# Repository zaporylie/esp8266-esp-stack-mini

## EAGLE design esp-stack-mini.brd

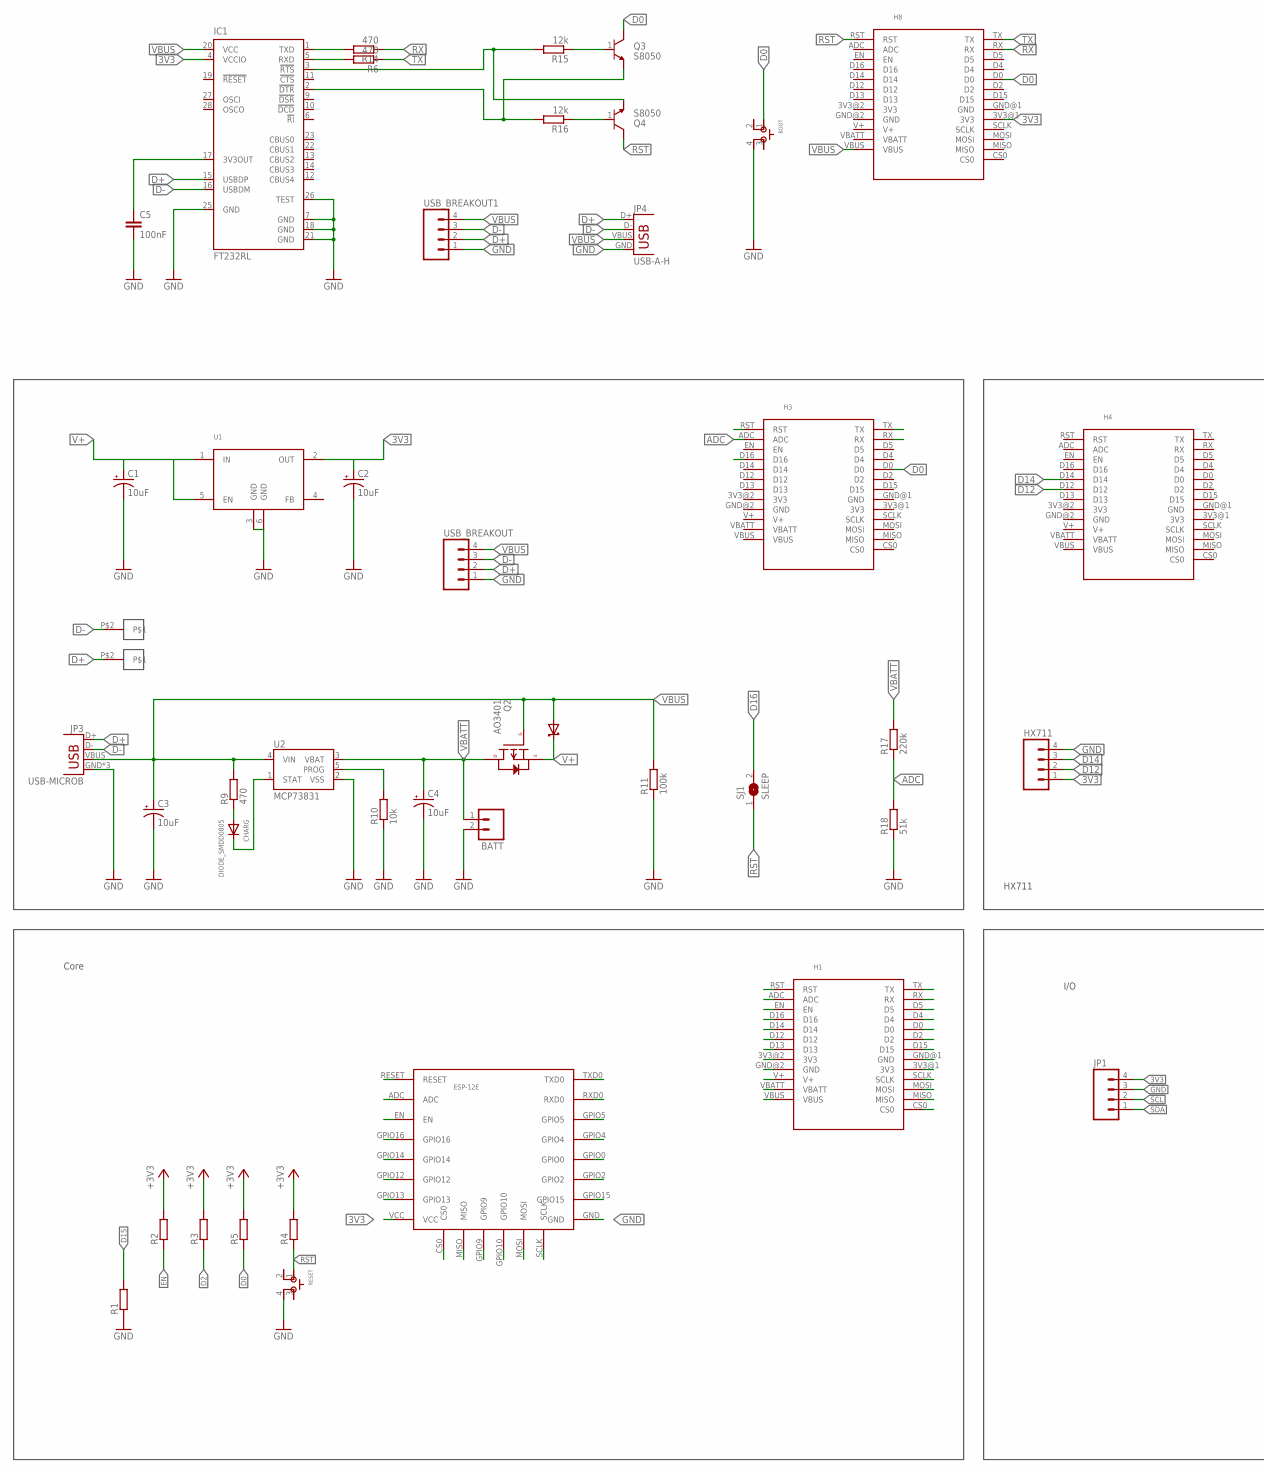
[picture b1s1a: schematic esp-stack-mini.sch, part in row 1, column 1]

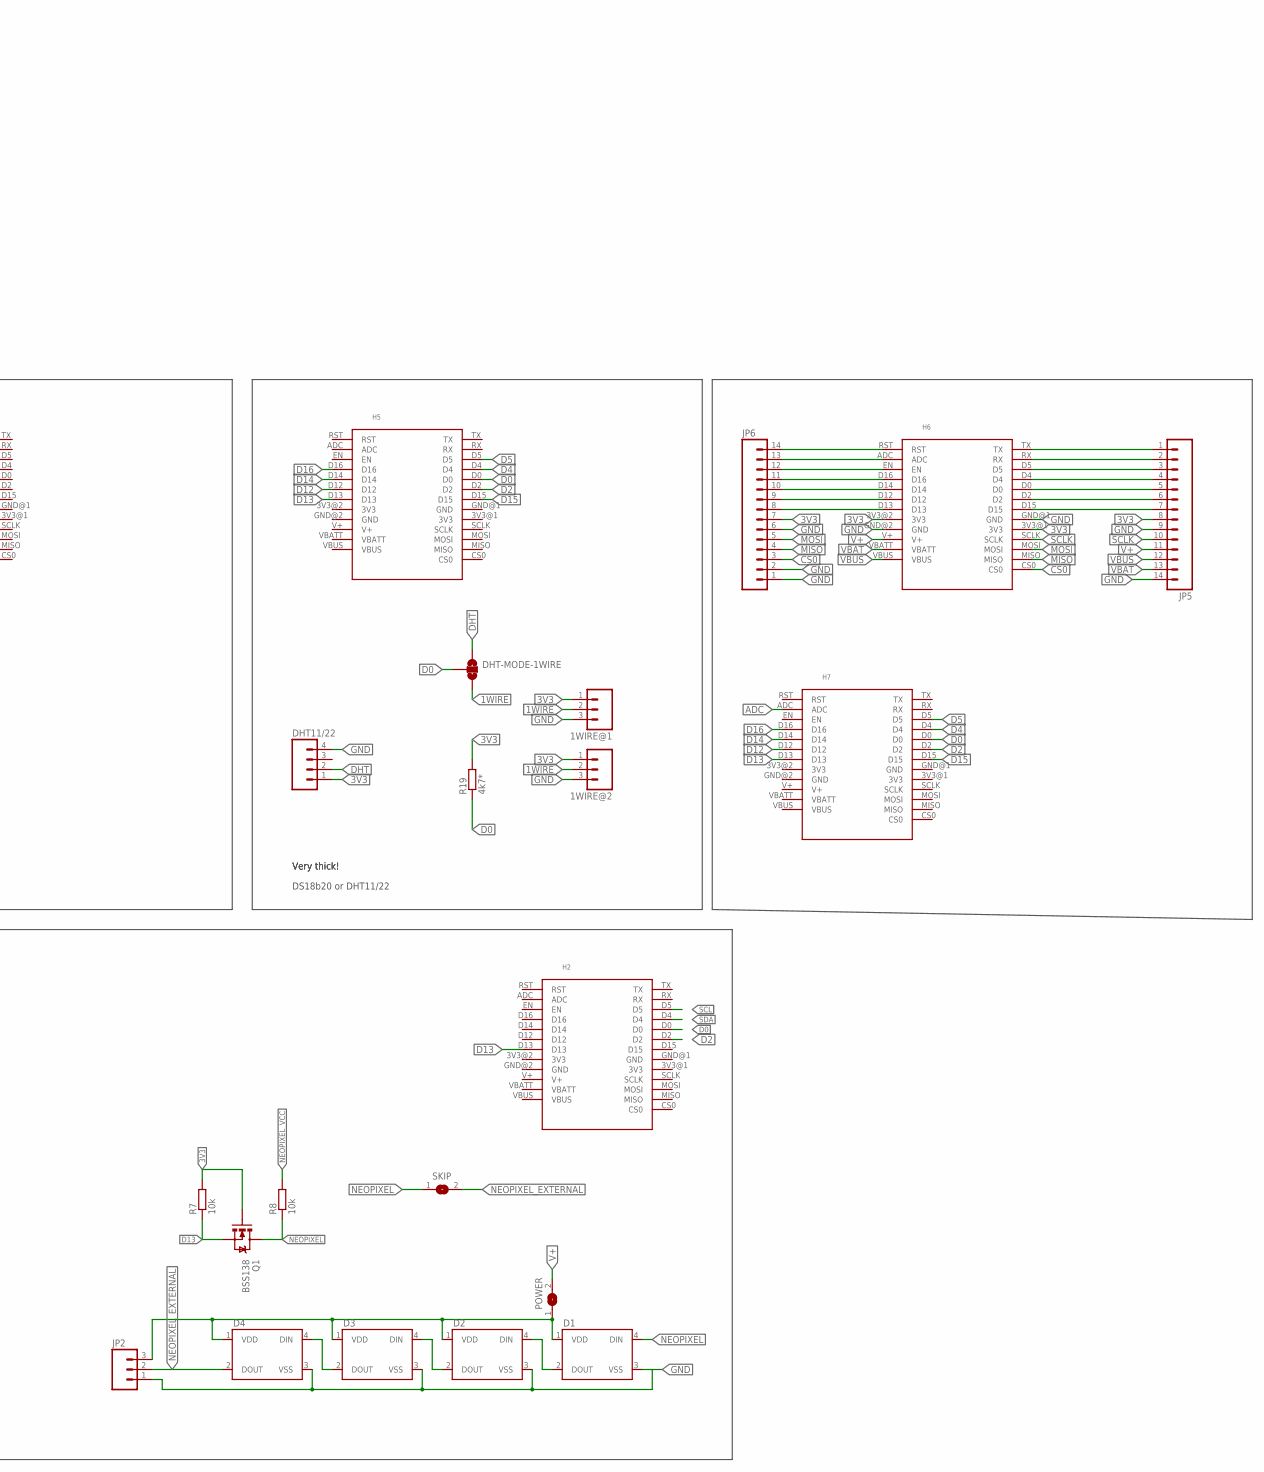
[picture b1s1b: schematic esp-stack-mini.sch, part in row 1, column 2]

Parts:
1WIRE@1, 1WIRE@2: M031X03_NO_SILK; 1X03_NO_SILK
BATT: M021X02_NO_SILK; 1X02_NO_SILK
BOOT: SKSCLDE010
C1, C2, C3, C4: 10uF; EIA3216
C5: 100nF; 0805
CHARG: DIODE_SMDD0805; D0805
D1, D2, D3, D4: WS2812B
D5: MBR120; SOD123
DHT11/22: M04NO_SILK_ALL_ROUND; 1X04_NO_SILK_ALL_ROUND
DHT-MODE-1WIRE: SOLDERJUMPER_2WAYT; SJ_2
ESP-12E: ESP-12E
H1, H2, H3, H4, H5, H6, H7, H8: ESP-BOARD
HX711: M04NO_SILK_ALL_ROUND; 1X04_NO_SILK_ALL_ROUND
IC1: FT232RL; SSOP28
JP1: M04NO_SILK_ALL_ROUND; 1X04_NO_SILK_ALL_ROUND
JP2: M031X03_NO_SILK; 1X03_NO_SILK
JP3: USB-MICROB
JP4: USB-A-H
JP5, JP6: M14; 1X14
POWER: SJ
Q1: BSS138; SOT23-3
Q2: AO3401; SOT23-3
Q3, Q4: S8050; SOT23-3
R1, R2, R3, R4, R5: R-EU_R0805; R0805
R6, R9, R14: 470; R0805
R7, R8, R10: 10k; R0805
R11: 100k; R0805
R15, R16: 12k; R0805
R17: 220k; R0805
R18: 51k; R0805
R19: 4k7*; R0805
RESET: SKSCLDE010
SJ1: SLEEP; SJ
SKIP: SJ
U1: TPS737XX; SOT223-6
U2: MCP73831; SOT23-5
U$2, U$3: POGO-PAD
USB_BREAKOUT, USB_BREAKOUT1: M04NO_SILK_ALL_ROUND; 1X04_NO_SILK_ALL_ROUND

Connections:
1WIRE: 1WIRE@1.2, 1WIRE@2.2, DHT-MODE-1WIRE.3
3V3: 1WIRE@1.1, 1WIRE@2.1, C2.A (+), DHT11/22.1, ESP-12E.VCC, H1.3V3@1 (3V3), H1.3V3@2 (3V3), H2.3V3@1 (3V3), H2.3V3@2 (3V3), H3.3V3@1 (3V3), H3.3V3@2 (3V3), H4.3V3@1 (3V3), H4.3V3@2 (3V3), H5.3V3@1 (3V3), H5.3V3@2 (3V3), H6.3V3@1 (3V3), H6.3V3@2 (3V3), H7.3V3@1 (3V3), H7.3V3@2 (3V3), H8.3V3@1 (3V3), H8.3V3@2 (3V3), HX711.1, IC1.4 (VCCIO), JP1.4, JP5.8, JP6.7, Q1.1 (G), R2.2, R3.2, R4.2, R5.2, R7.2, R19.2, U1.2 (OUT)
ADC: ESP-12E.ADC, H1.ADC, H3.ADC, H7.ADC, R17.1, R18.2
CS0: ESP-12E.CS0, H1.CS0, H6.CS0, JP6.3
D0: BOOT.1, DHT-MODE-1WIRE.2, ESP-12E.GPIO0, H1.D0, H2.D0, H3.D0, H5.D0, H7.D0, H8.D0, Q3.3, R5.1, R19.1
D2: ESP-12E.GPIO2, H1.D2, H2.D2, H5.D2, H7.D2, R3.1
D4: ESP-12E.GPIO4, H1.D4, H5.D4, H7.D4
D5: ESP-12E.GPIO5, H1.D5, H5.D5, H7.D5
D9: ESP-12E.GPIO9
D10: ESP-12E.GPIO10
D12: ESP-12E.GPIO12, H1.D12, H4.D12, H5.D12, H7.D12, HX711.2
D13: ESP-12E.GPIO13, H1.D13, H2.D13, H5.D13, H7.D13, Q1.2 (S), R7.1
D14: ESP-12E.GPIO14, H1.D14, H4.D14, H5.D14, H7.D14, HX711.3
D15: ESP-12E.GPIO15, H1.D15, H5.D15, H7.D15, R1.2
D16: ESP-12E.GPIO16, H1.D16, H3.D16, H5.D16, H7.D16, SJ1.2
D+: IC1.15 (USBDP), JP3.D+, JP4.D+, U$3.P$2, USB_BREAKOUT.2, USB_BREAKOUT1.2
D-: IC1.16 (USBDM), JP3.D-, JP4.D-, U$2.P$2, USB_BREAKOUT.3, USB_BREAKOUT1.3
DHT: DHT11/22.2, DHT-MODE-1WIRE.1
EN: ESP-12E.EN, H1.EN, R2.1
GND: 1WIRE@1.3, 1WIRE@2.3, BATT.2, BOOT.4 (3), C1.C (-), C2.C (-), C3.C (-), C4.C (-), C5.2, D1.3 (VSS), D2.3 (VSS), D3.3 (VSS), D4.3 (VSS), DHT11/22.4, ESP-12E.GND, H1.GND@1 (GND), H1.GND@2 (GND), H2.GND@1 (GND), H2.GND@2 (GND), H3.GND@1 (GND), H3.GND@2 (GND), H4.GND@1 (GND), H4.GND@2 (GND), H5.GND@1 (GND), H5.GND@2 (GND), H6.GND@1 (GND), H6.GND@2 (GND), H7.GND@1 (GND), H7.GND@2 (GND), H8.GND@1 (GND), H8.GND@2 (GND), HX711.4, IC1.7 (GND), IC1.18 (GND), IC1.21 (GND), IC1.25 (GND), IC1.26 (TEST), JP1.3, JP2.1, JP3.GND, JP3.MT1 (GND), JP3.MT2 (GND), JP4.GND, JP5.9, JP5.14, JP6.1, JP6.2, JP6.6, R1.1, R10.1, R11.1, R18.1, RESET.4 (3), U1.3 (GND), U1.6 (GND), U2.2 (VSS), USB_BREAKOUT.1, USB_BREAKOUT1.1
MISO: ESP-12E.MISO, H1.MISO, H6.MISO, JP6.4
MOSI: ESP-12E.MOSI, H1.MOSI, H6.MOSI, JP6.5
unnamed: D1.2 (DOUT), D2.4 (DIN)
unnamed: D2.2 (DOUT), D3.4 (DIN)
unnamed: D3.2 (DOUT), D4.4 (DIN)
unnamed: IC1.5 (RXD), R6.2
unnamed: R10.2, U2.5 (PROG)
unnamed: CHARG.A, R9.1
unnamed: CHARG.K, U2.1 (STAT)
unnamed: Q4.1, R16.1
unnamed: Q3.1, R15.1
unnamed: C5.1, IC1.17 (3V3OUT)
unnamed: IC1.1 (TXD), R14.2
unnamed: IC1.3 (!RTS), Q4.2, R15.2
unnamed: IC1.2 (!DTR), Q3.2, R16.2
unnamed: H6.TX, JP5.1
unnamed: H6.RX, JP5.2
unnamed: H6.D5, JP5.3
unnamed: H6.D4, JP5.4
unnamed: H6.D0, JP5.5
unnamed: H6.D2, JP5.6
unnamed: H6.D15, JP5.7
unnamed: H6.RST, JP6.14
unnamed: H6.ADC, JP6.13
unnamed: H6.EN, JP6.12
unnamed: H6.D16, JP6.11
unnamed: H6.D14, JP6.10
unnamed: H6.D12, JP6.9
unnamed: H6.D13, JP6.8
NEOPIXEL: D1.4 (DIN), Q1.3 (D), R8.1, SKIP.1
NEOPIXEL_EXTERNAL: D4.2 (DOUT), JP2.2, SKIP.2
NEOPIXEL_VCC: D1.1 (VDD), D2.1 (VDD), D3.1 (VDD), D4.1 (VDD), JP2.3, POWER.1, R8.2
RST: ESP-12E.RESET, H1.RST, H3.RST, H8.RST, Q4.3, R4.1, RESET.1, SJ1.1
RX: ESP-12E.RXD0, H1.RX, H3.RX, H8.RX, R14.1
SCL: H2.D5, JP1.2
SCLK: ESP-12E.SCLK, H1.SCLK, H6.SCLK, JP5.10
SDA: H2.D4, JP1.1
TX: ESP-12E.TXD0, H1.TX, H3.TX, H8.TX, R6.1
V+: C1.A (+), D5.C, H1.V+, H2.V+, H3.V+, H4.V+, H5.V+, H6.V+, H7.V+, H8.V+, JP5.11, POWER.2, Q2.2 (S), U1.1 (IN), U1.5 (EN)
VBAT: H6.VBATT, JP5.13
VBATT: BATT.1, C4.A (+), H1.VBATT, H2.VBATT, H3.VBATT, H4.VBATT, H5.VBATT, H7.VBATT, H8.VBATT, Q2.3 (D), R17.2, U2.3 (VBAT)
VBUS: C3.A (+), D5.A, H1.VBUS, H2.VBUS, H3.VBUS, H4.VBUS, H5.VBUS, H6.VBUS, H7.VBUS, H8.VBUS, IC1.20 (VCC), JP3.VBUS, JP4.VBUS, JP5.12, Q2.1 (G), R9.2, R11.2, U2.4 (VIN), USB_BREAKOUT.4, USB_BREAKOUT1.4

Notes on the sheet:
Core
I/O
Very thick!
DS18b20 or DHT11/22
HX711

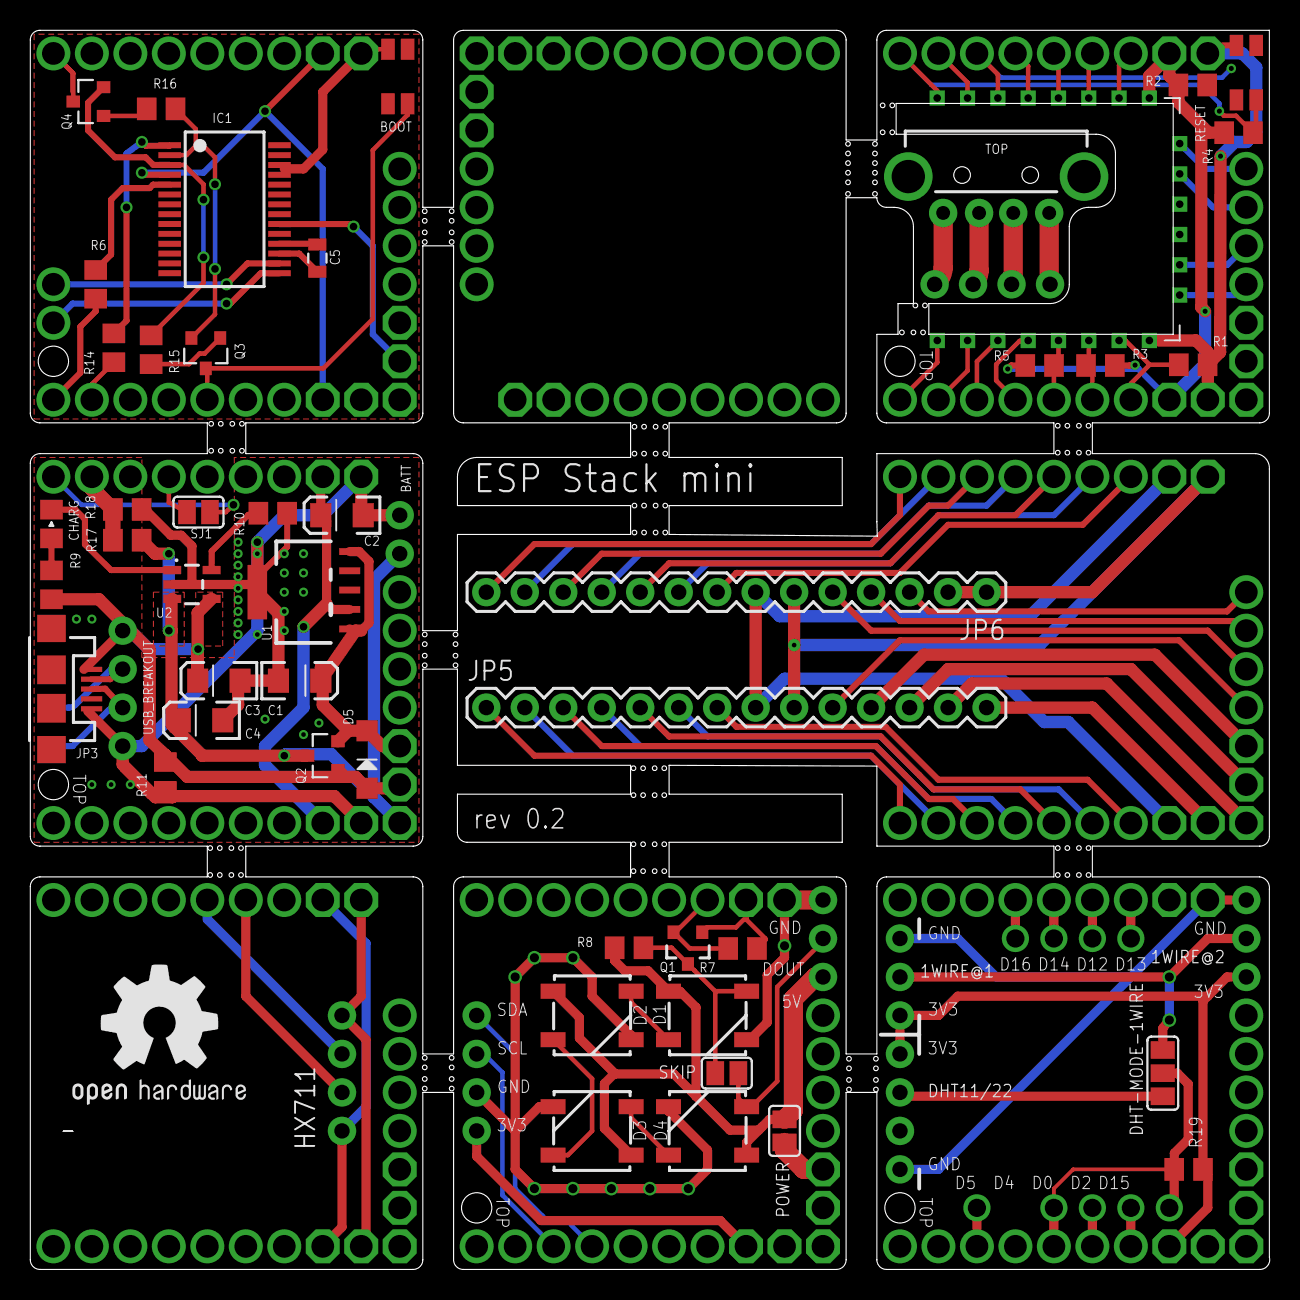
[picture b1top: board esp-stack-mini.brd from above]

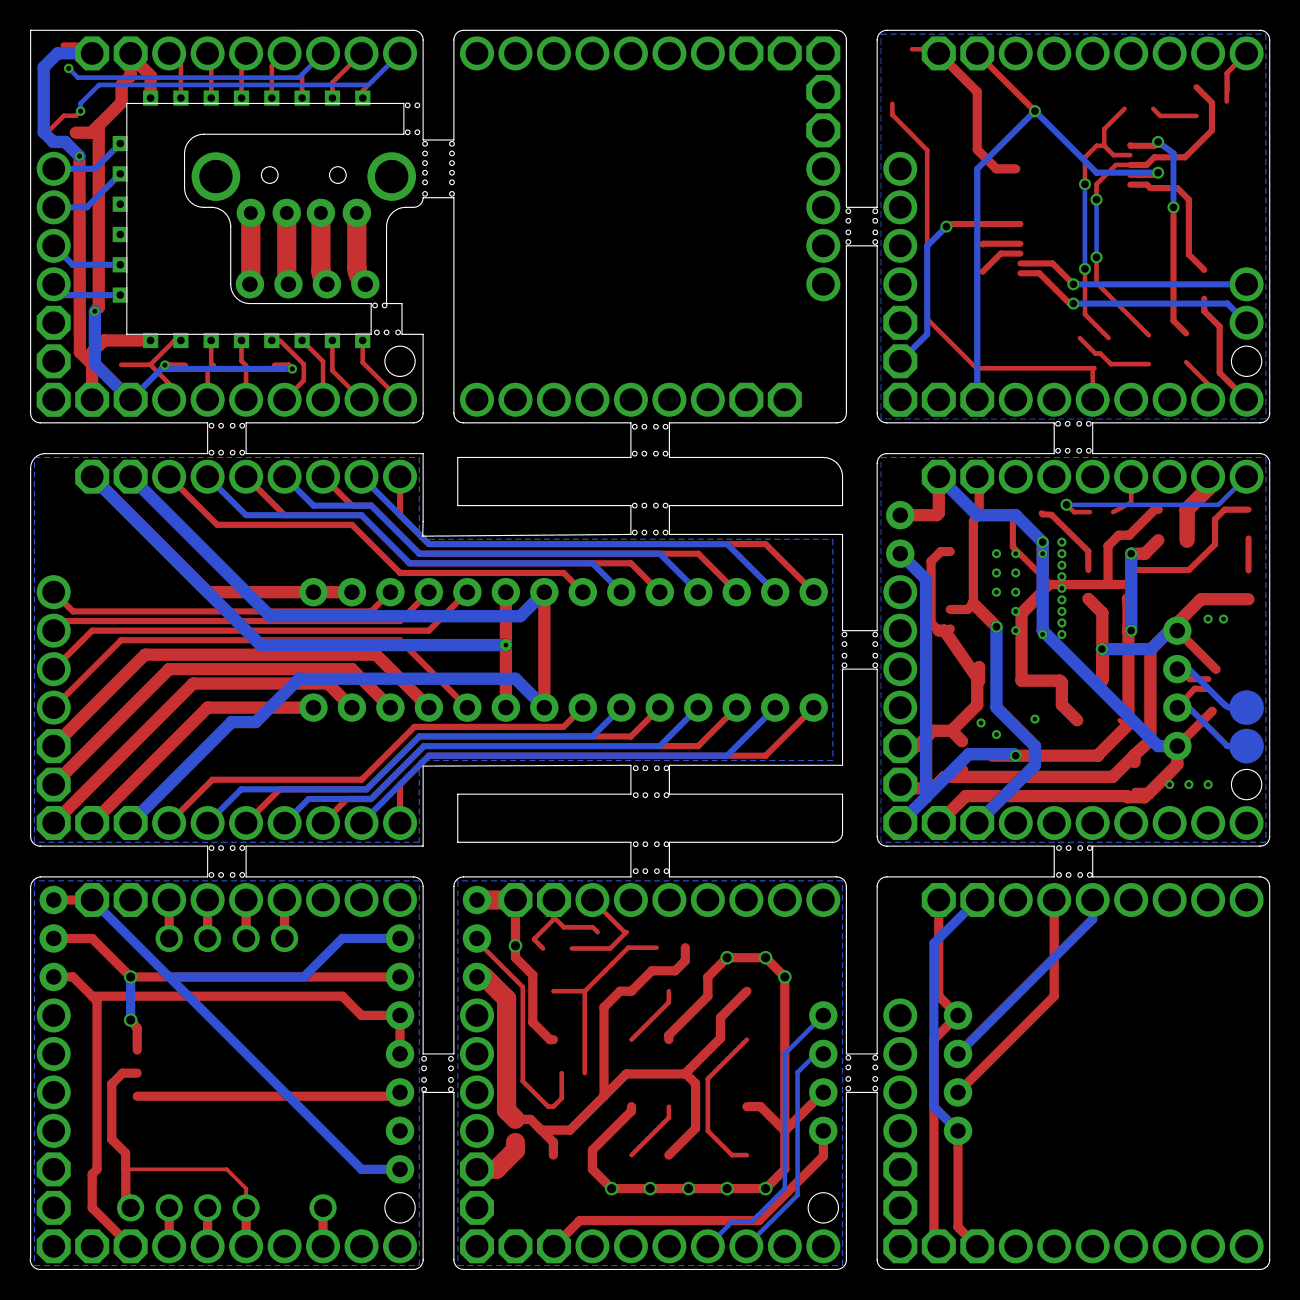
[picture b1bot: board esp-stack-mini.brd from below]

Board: 2 copper layers, 81.8 x 81.8 mm, 66 parts (4 on the bottom side), 60 nets.

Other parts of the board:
U$1: OSHW1

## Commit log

2015-08-04 Inital commit
2015-08-04 USB/Battery board all-connected
2015-08-29 First prototype
2015-12-11 progress

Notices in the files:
parts and their libraries:
SparkFun-Connectors: Licensing: Creative Commons ShareAlike 4.0 International - https://creativecommons.org/licenses/by-sa/4.0
